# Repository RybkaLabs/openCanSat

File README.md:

# openCanSat
universal and powerful kit for the CanSat competition

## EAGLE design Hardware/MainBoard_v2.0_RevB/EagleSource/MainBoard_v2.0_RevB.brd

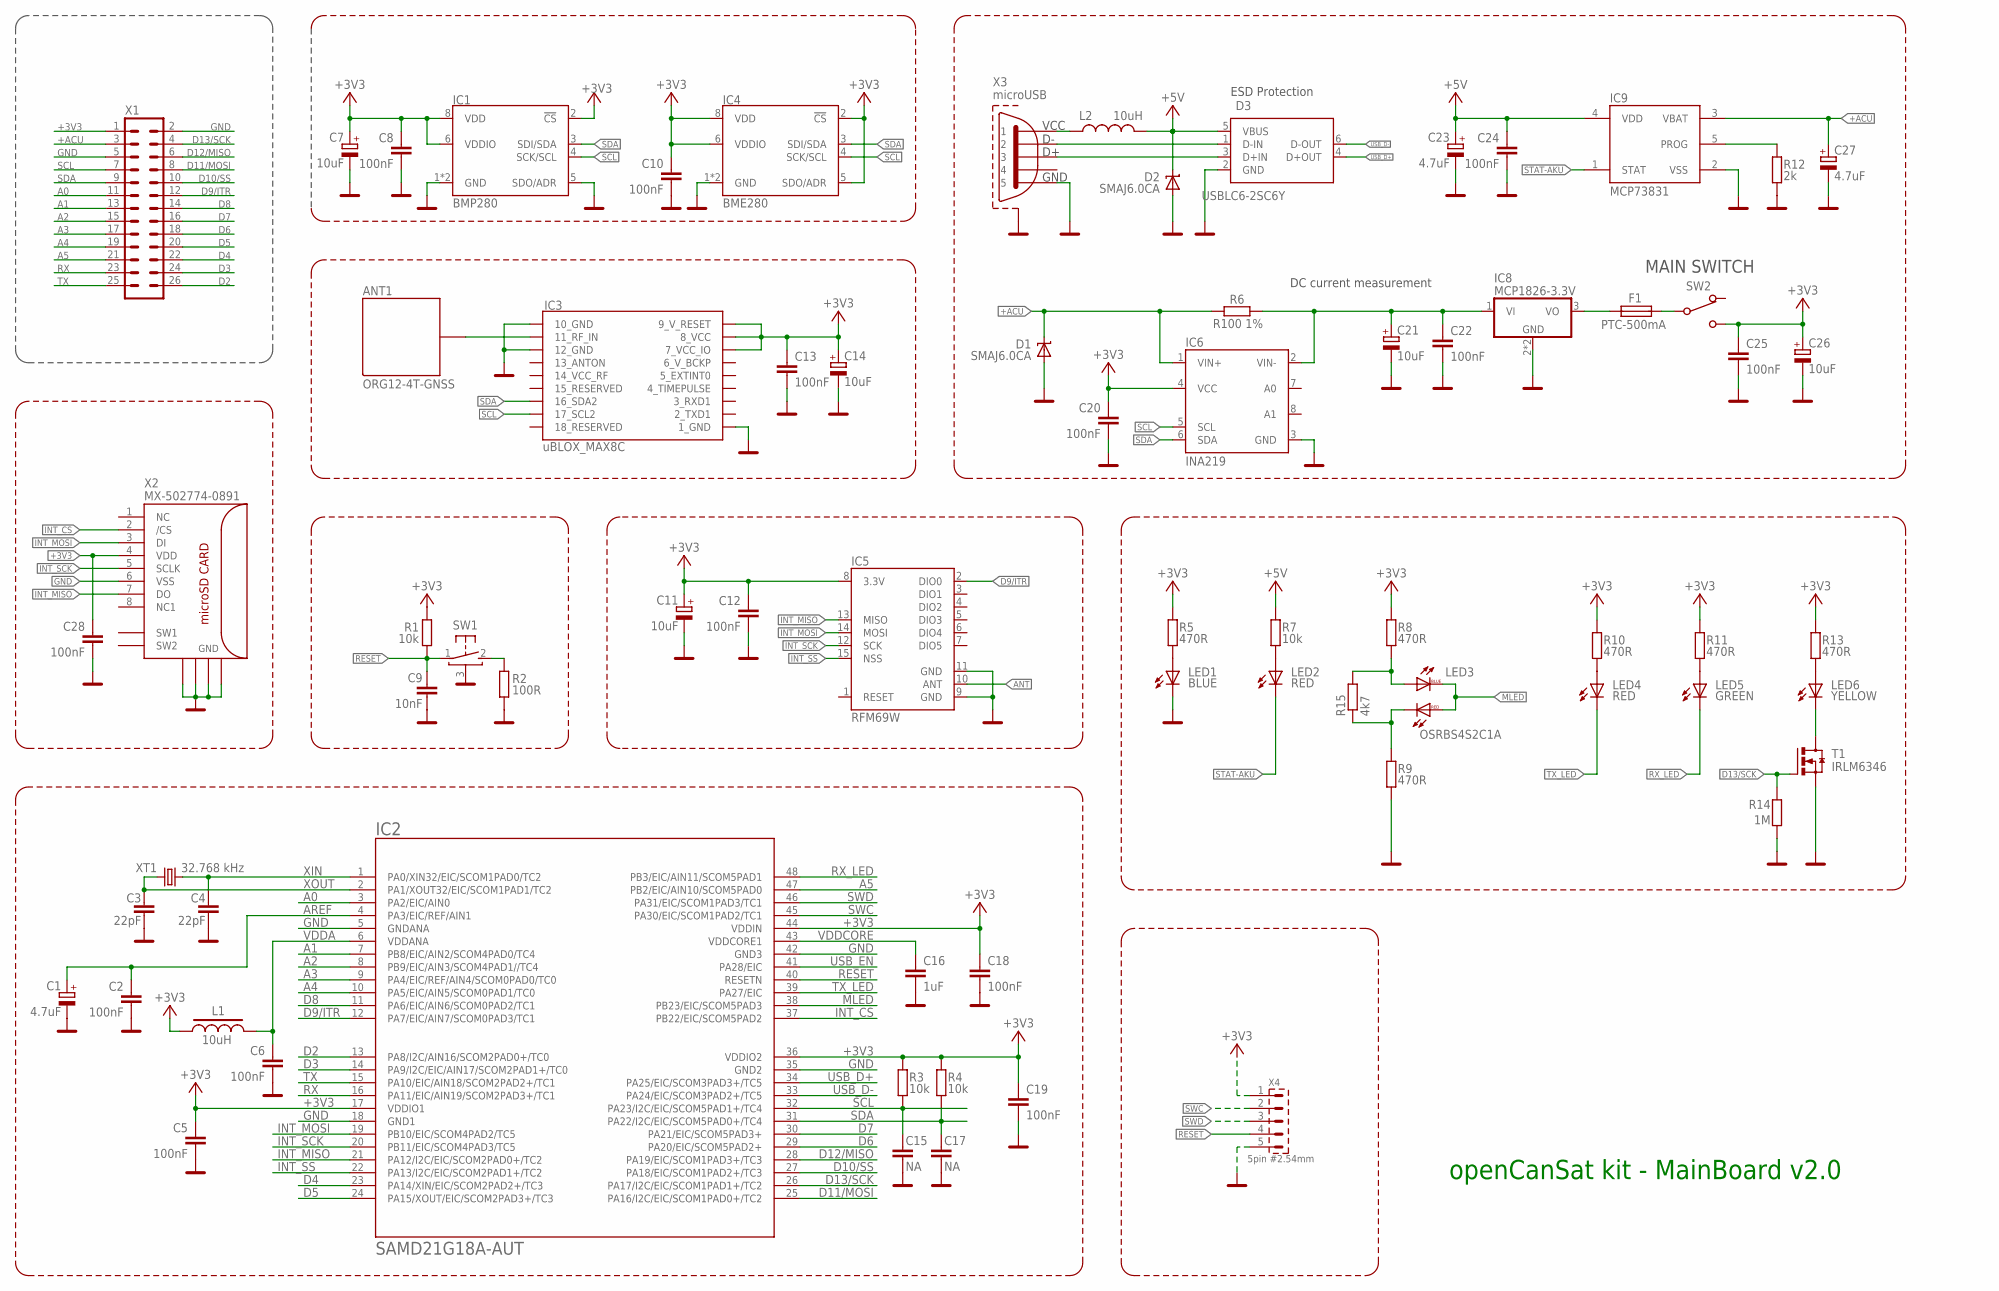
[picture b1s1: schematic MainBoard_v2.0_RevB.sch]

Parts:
ANT1: ORG12-4T-GNSS; ANT_GPS_12X12
C1, C23, C27: 4.7uF; SMC_A
C2, C5, C6, C8, C10, C12, C13, C18, C19, C20, C22, C24, C25, C28: 100nF; C0603
C3, C4: 22pF; C0603
C7, C11, C14: 10uF; SMC_A
C9: 10nF; C0603
C15, C17: NA; C0603
C16: 1uF; C0805
C21, C26: 10uF; SMC_B
D1, D2: SMAJ6.0CA; DO214AC
D3: USBLC6-2SC6Y; SOT95P280X145-6N
F1: PTC-500mA; 1210
IC1: BMP280; LGA-8-2.5X2.5
IC2: SAMD21G18A-AUT; TQFP48-7X7
IC3: uBLOX_MAX8C; UBLOX_MAX-6
IC4: BME280; LGA-8-2.5X2.5
IC5: RFM69W; RFM69W-XXXS2
IC6: INA219; SOT23-8
IC8: MCP1826-3.3V; SOT223-3
IC9: MCP73831; SOT23-5L
L1, L2: 10uH; R0805
LED1: BLUE; CHIPLED_0603
LED2, LED4: RED; CHIPLED_0603
LED3: OSRBS4S2C1A; PLCC4
LED5: GREEN; CHIPLED_0603
LED6: YELLOW; CHIPLED_0603
R1, R3, R4, R7: 10k; R0603
R2: 100R; R0603
R5, R8, R9, R10, R11, R13: 470R; R0603
R6: R100 1%; R2010
R12: 2k; R0603
R14: 1M; R0603
R15: 4k7; R0603
SW1: B3U-3100P; B3U-3100PM
SW2: MSS-1290
T1: IRLM6346; SOT23
X1: MA13-2SMD; MA13-2
X2: MX-502774-0891; 502774-0891
X3: microUSB; 1981568-MICROUSB
X4: 5pin #2.54mm; PIN5
XT1: 32.768 kHz; XTAL35X15

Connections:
3V31: F1.P$1 (1), IC8.3 (VO)
3V32: F1.P$2 (2), SW2.2 (2-COM)
+3V3: C5.1, C7.+, C8.1, C10.1, C11.+, C12.1, C13.1, C14.+, C18.1, C19.1, C20.1, C25.1, C26.+, C28.1, IC1.2 (!CS), IC1.6 (VDDIO), IC1.8 (VDD), IC2.17 (VDDIO1), IC2.36 (VDDIO2), IC2.44 (VDDIN), IC3.7_VCC_IO, IC3.8_VCC, IC3.9_V_RESET, IC4.2 (!CS), IC4.5 (SDO/ADR), IC4.6 (VDDIO), IC4.8 (VDD), IC5.8 (3.3V), IC6.4 (VCC), L1.1, R1.2, R3.2, R4.2, R5.2, R8.2, R10.2, R11.2, R13.2, SW2.1 (1-NO), X1.1, X2.4 (VDD), X4.1
+5V: C23.+, C24.1, D2.C, D3.5 (VBUS), IC9.4 (VDD), L2.2, R7.2
+ACU: C27.+, D1.C, IC6.1 (VIN+), IC9.3 (VBAT), R6.1, X1.3
+VUSB: L2.1, X3.P$1 (1)
A0: IC2.3 (PA2/EIC/AIN0), X1.11
A1: IC2.7 (PB8/EIC/AIN2/SCOM4PAD0/TC4), X1.13
A2: IC2.8 (PB9/EIC/AIN3/SCOM4PAD1//TC4), X1.15
A3: IC2.9 (PA4/EIC/REF/AIN4/SCOM0PAD0/TC0), X1.17
A4: IC2.10 (PA5/EIC/AIN5/SCOM0PAD1/TC0), X1.19
A5: IC2.47 (PB2/EIC/AIN10/SCOM5PAD0), X1.21
ANT: IC5.10 (ANT)
ANT_GPS: ANT1.ANT_GPS, IC3.11_RF_IN
AREF: C1.+, C2.1, IC2.4 (PA3/EIC/REF/AIN1)
D2: IC2.13 (PA8/I2C/AIN16/SCOM2PAD0+/TC0), X1.26
D3: IC2.14 (PA9/I2C/EIC/AIN17/SCOM2PAD1+/TC0), X1.24
D4: IC2.23 (PA14/XIN/EIC/SCOM2PAD2+/TC3), X1.22
D5: IC2.24 (PA15/XOUT/EIC/SCOM2PAD3+/TC3), X1.20
D6: IC2.29 (PA20/EIC/SCOM5PAD2+), X1.18
D7: IC2.30 (PA21/EIC/SCOM5PAD3+), X1.16
D8: IC2.11 (PA6/EIC/AIN6/SCOM0PAD2/TC1), X1.14
D9/ITR: IC2.12 (PA7/EIC/AIN7/SCOM0PAD3/TC1), IC5.2 (DIO0), X1.12
D10/SS: IC2.27 (PA18/EIC/SCOM1PAD2+/TC3), X1.10
D11/MOSI: IC2.25 (PA16/I2C/EIC/SCOM1PAD0+/TC2), X1.8
D12/MISO: IC2.28 (PA19/EIC/SCOM1PAD3+/TC3), X1.6
D13/SCK: IC2.26 (PA17/I2C/EIC/SCOM1PAD1+/TC2), R14.2, T1.1 (G), X1.4
D+IN: D3.3 (D+IN), X3.P$3 (3)
D-IN: D3.1 (D-IN), X3.P$2 (2)
GND: C1.-, C2.2, C3.2, C4.2, C5.2, C6.2, C7.-, C8.2, C9.2, C10.2, C11.-, C12.2, C13.2, C14.-, C15.2, C16.2, C17.2, C18.2, C19.2, C20.2, C21.-, C22.2, C23.-, C24.2, C25.2, C26.-, C27.-, C28.2, D1.A, D2.A, D3.2 (GND), IC1.1 (GND), IC1.5 (SDO/ADR), IC1.7 (GND), IC2.5 (GNDANA), IC2.18 (GND1), IC2.35 (GND2), IC2.42 (GND3), IC3.1_GND, IC3.10_GND, IC3.12_GND, IC4.1 (GND), IC4.7 (GND), IC5.9 (GND), IC5.11 (GND), IC6.3 (GND), IC8.2 (GND), IC8.4 (GND), IC9.2 (VSS), LED1.C, R2.1, R9.1, R12.1, R14.1, SW1.3, T1.2 (S), X1.2, X1.5, X2.6 (VSS), X2.GND1, X2.GND2, X2.GND3, X2.GND4, X3.P$5 (5), X3.P$6 (SHIELD), X3.P$7 (SHIELD), X3.P$8 (SHIELD), X3.P$9 (SHIELD), X3.P$10 (SHIELD), X3.P$11 (SHIELD), X4.5
INT_CS: IC2.37 (PB22/EIC/SCOM5PAD2), X2.2 (/CS)
INT_MISO: IC2.21 (PA12/I2C/EIC/SCOM2PAD0+/TC2), IC5.13 (MISO), X2.7 (DO)
INT_MOSI: IC2.19 (PB10/EIC/SCOM4PAD2/TC5), IC5.14 (MOSI), X2.3 (DI)
INT_SCK: IC2.20 (PB11/EIC/SCOM4PAD3/TC5), IC5.12 (SCK), X2.5 (SCLK)
INT_SS: IC2.22 (PA13/I2C/EIC/SCOM2PAD1+/TC2), IC5.15 (NSS)
MLED: IC2.38 (PB23/EIC/SCOM5PAD3), LED3.3 (C-B), LED3.4 (A-R)
unnamed: LED4.A, R10.1
unnamed: LED5.A, R11.1
unnamed: LED6.A, R13.1
unnamed: LED6.C, T1.3 (D)
unnamed: R2.2, SW1.2 (S)
unnamed: LED3.2 (A-B), R8.1, R15.2
unnamed: LED3.1 (C-R), R9.2, R15.1
unnamed: LED2.A, R7.1
unnamed: LED1.A, R5.1
unnamed: C21.+, C22.1, IC6.2 (VIN-), IC8.1 (VI), R6.2
unnamed: IC9.5 (PROG), R12.2
RESET: C9.1, IC2.40 (RESETN), R1.1, SW1.1, X4.4
RX: IC2.16 (PA11/EIC/AIN19/SCOM2PAD3+/TC1), X1.23
RX_LED: IC2.48 (PB3/EIC/AIN11/SCOM5PAD1), LED5.C
SCL: C15.1, IC1.4 (SCK/SCL), IC2.32 (PA23/I2C/EIC/SCOM5PAD1+/TC4), IC3.17_SCL2, IC4.4 (SCK/SCL), IC6.5 (SCL), R3.1, X1.7
SDA: C17.1, IC1.3 (SDI/SDA), IC2.31 (PA22/I2C/EIC/SCOM5PAD0+/TC4), IC3.16_SDA2, IC4.3 (SDI/SDA), IC6.6 (SDA), R4.1, X1.9
STAT-AKU: IC9.1 (STAT), LED2.C
SWC: IC2.45 (PA30/EIC/SCOM1PAD2/TC1), X4.2
SWD: IC2.46 (PA31/EIC/SCOM1PAD3/TC1), X4.3
TX: IC2.15 (PA10/EIC/AIN18/SCOM2PAD2+/TC1), X1.25
TX_LED: IC2.39 (PA27/EIC), LED4.C
USB_D+: D3.4 (D+OUT), IC2.34 (PA25/EIC/SCOM3PAD3+/TC5)
USB_D-: D3.6 (D-OUT), IC2.33 (PA24/EIC/SCOM3PAD2+/TC5)
USB_EN: IC2.41 (PA28/EIC)
VDDA: C6.1, IC2.6 (VDDANA), L1.2
VDDCORE: C16.1, IC2.43 (VDDCORE1)
XIN: C4.1, IC2.1 (PA0/XIN32/EIC/SCOM1PAD0/TC2), XT1.2
XOUT: C3.1, IC2.2 (PA1/XOUT32/EIC/SCOM1PAD1/TC2), XT1.1

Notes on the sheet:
openCanSat kit - MainBoard v2.0
ESD Protection
MAIN SWITCH
DC current measurement

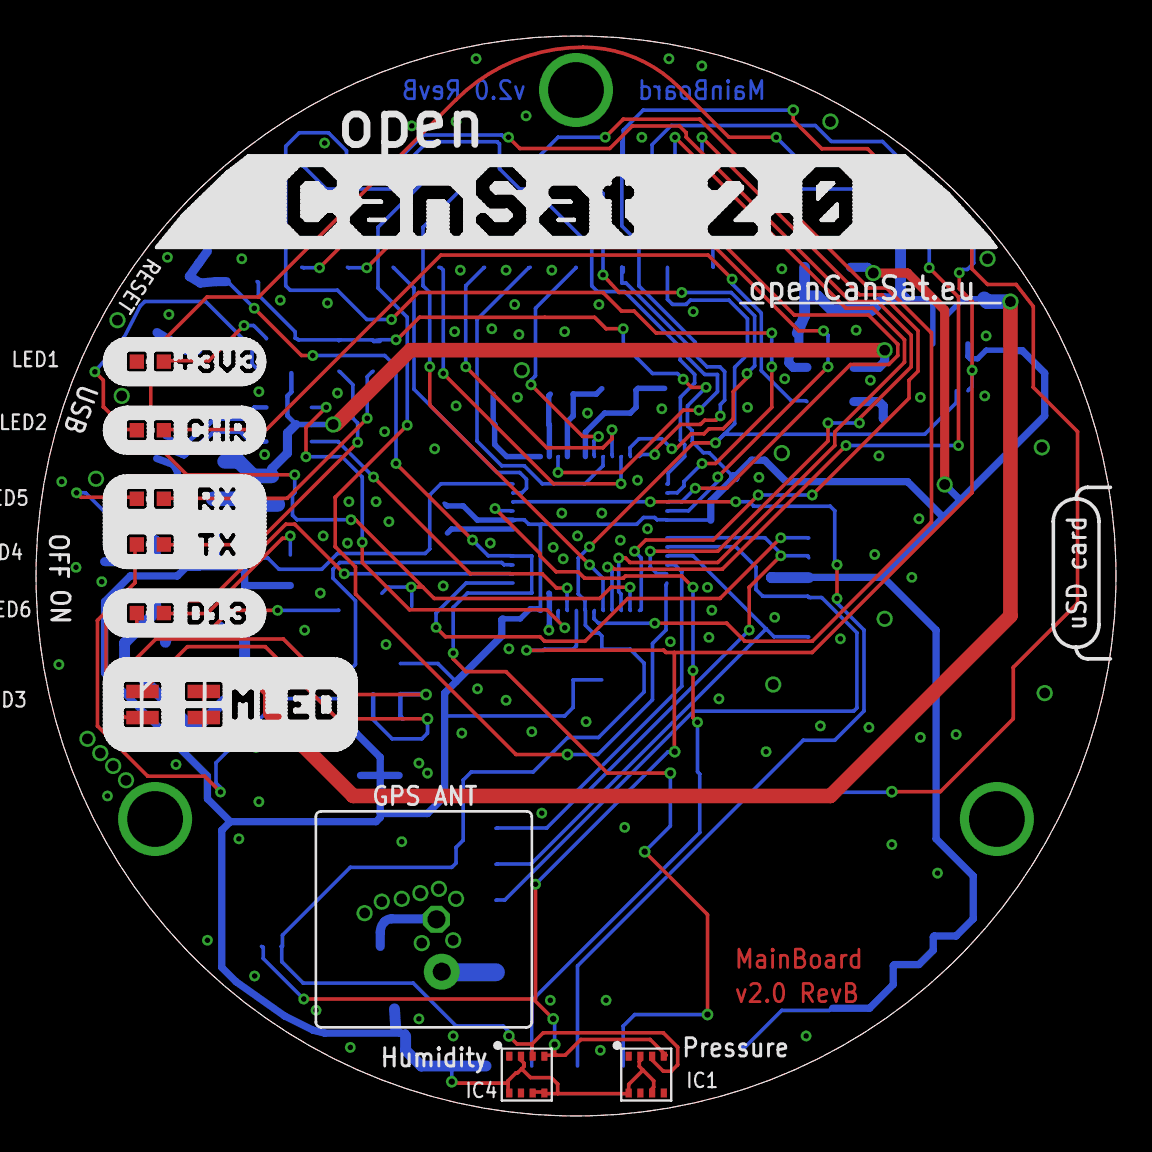
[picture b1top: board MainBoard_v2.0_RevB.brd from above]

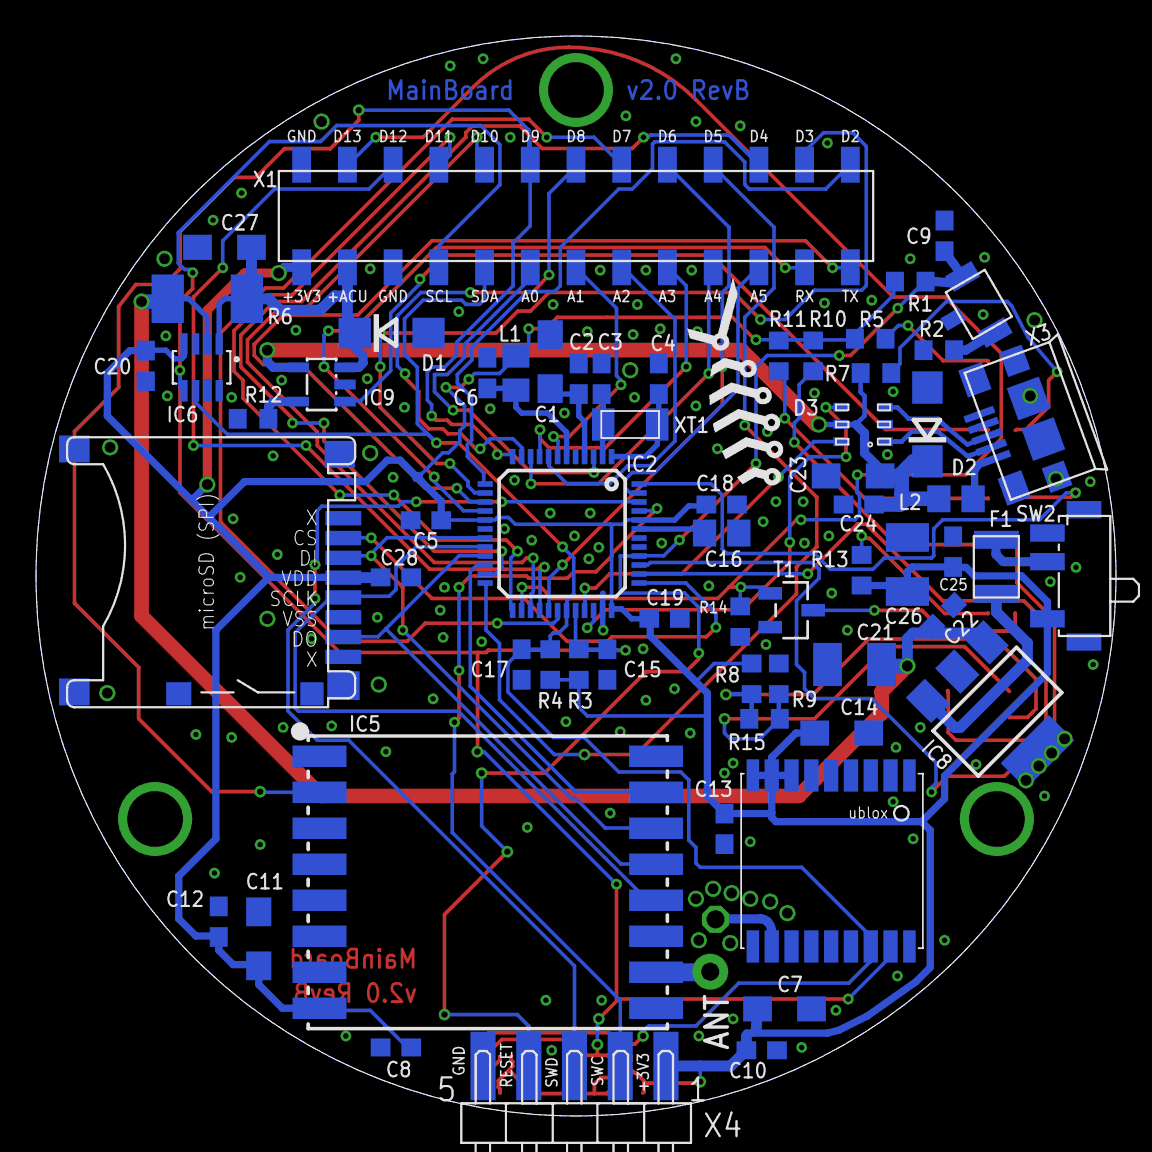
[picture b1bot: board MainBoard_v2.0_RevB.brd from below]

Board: 2 copper layers, 60.0 x 60.0 mm, 73 parts (64 on the bottom side), 62 nets.

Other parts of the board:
U$1: RYBICKA_12MM

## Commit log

2017-11-05 HW/MainBoard_v2.0_RevB

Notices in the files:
parts and their libraries:
SparkFun-Sensors: Licensing: Creative Commons ShareAlike 4.0 International - https://creativecommons.org/licenses/by-sa/4.0
Copyright (C) PaJa 2011-2014
Copyright (C) PaJa 2001-2014
